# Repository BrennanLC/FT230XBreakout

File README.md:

FT230XBreakout
==============

FT230X USB to Serial Breakout Board

Please refer to FT230X datasheet for information on output pin functions
of the FT230X. Board uses SSOP package of the FT230X.

Layout tested and verified on 11/16/13

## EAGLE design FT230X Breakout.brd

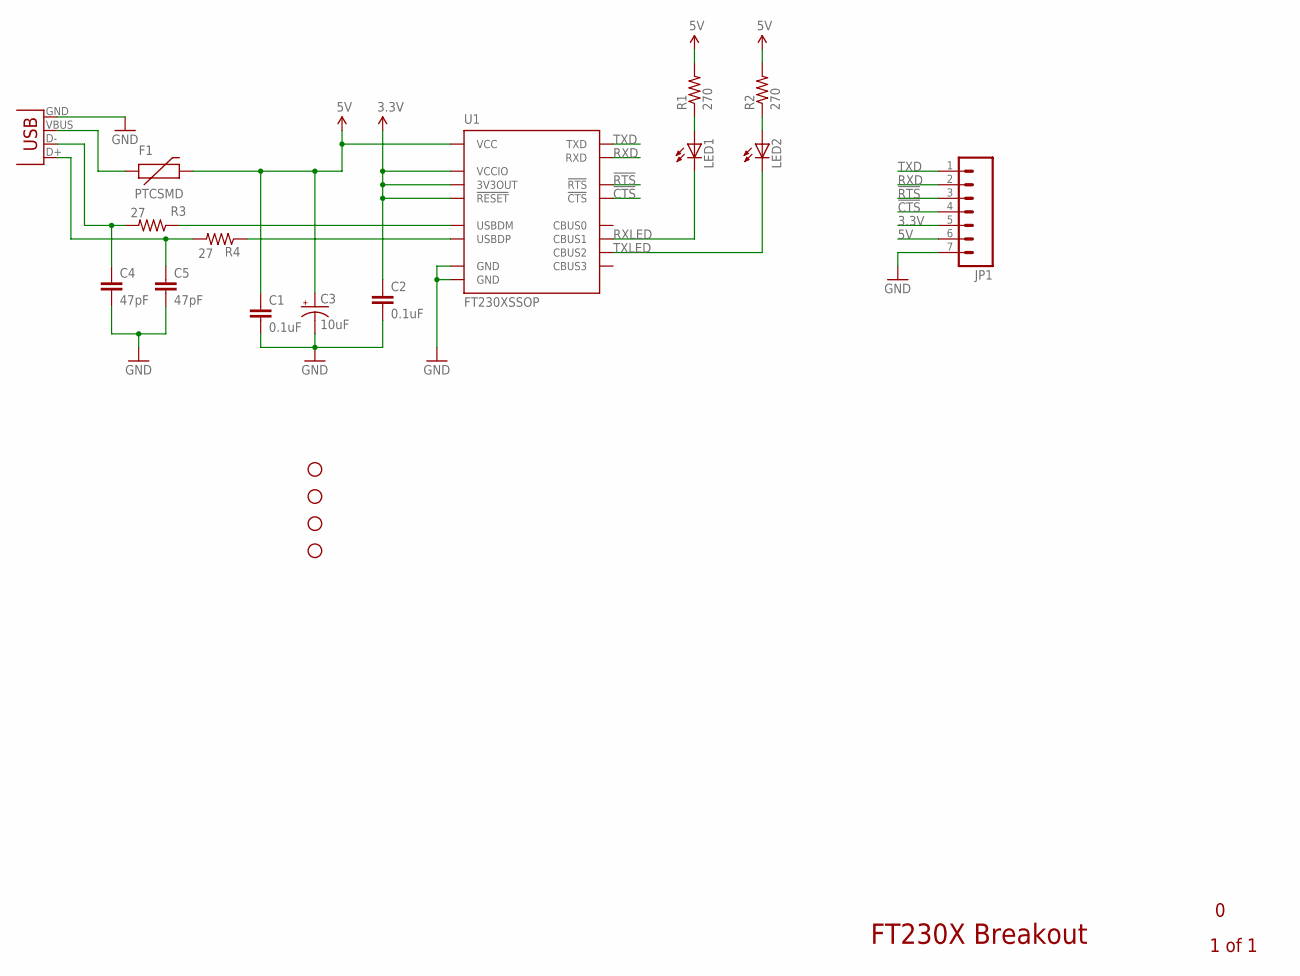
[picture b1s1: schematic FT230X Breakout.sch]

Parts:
C1, C2: 0.1uF; 0603-CAP
C3: 10uF; EIA3216-KIT
C4, C5: 47pF; 0603-CAP
F1: PTCSMD; PTC-1206
JP1: M07; 1X07
JP2: USBSMD; USB-MINIB
LED1, LED2: LED0603; LED-0603
R1, R2: 270; 0603-RES
R3, R4: 27; 0603-RES
STANDOFF1, STANDOFF2, STANDOFF3, STANDOFF4: STAND-OFF
U1: FT230XSSOP; SSOP16

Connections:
3.3V: C2.1, JP1.5, U1.3 (VCCIO), U1.10 (3V3OUT), U1.11 (!RESET)
5V: C1.1, C3.A (+), F1.2, JP1.6, R1.2, R2.2, U1.12 (VCC)
!CTS: JP1.4, U1.6 (!CTS)
!RTS: JP1.3, U1.2 (!RTS)
GND: C1.2, C2.2, C3.C (-), C4.2, C5.2, JP1.7, JP2.GND, U1.5 (GND), U1.13 (GND)
unnamed: F1.1, JP2.VBUS
unnamed: C4.1, JP2.D-, R3.2
unnamed: C5.1, JP2.D+, R4.2
unnamed: R4.1, U1.8 (USBDP)
unnamed: R3.1, U1.9 (USBDM)
unnamed: LED2.A, R2.1
unnamed: LED1.A, R1.1
RXD: JP1.2, U1.4 (RXD)
RXLED: LED1.C, U1.14 (CBUS1)
TXD: JP1.1, U1.1 (TXD)
TXLED: LED2.C, U1.7 (CBUS2)

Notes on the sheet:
FT230X Breakout
1 of 1

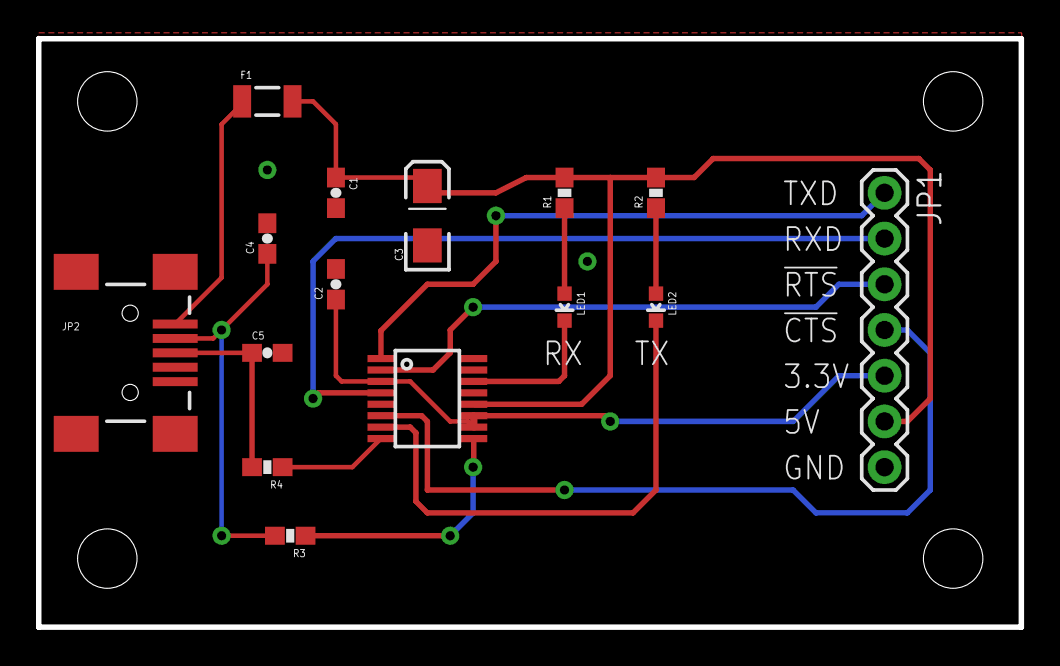
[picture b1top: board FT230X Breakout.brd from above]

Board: 2 copper layers, 54.6 x 32.7 mm, 19 parts (0 on the bottom side), 16 nets.

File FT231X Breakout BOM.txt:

Partlist exported from C:/Users/BrennanLC2/Documents/GitHub/FT231XBreakout/FT231X Breakout.sch at 11/3/2013 5:31:38 PM

Part      Value        Device           Package          Description                                                                                                                                               
C1        0.1uF        CAP0603-CAP      0603-CAP         Capacitor                                                                                                                                                 
C2        0.1uF        CAP0603-CAP      0603-CAP         Capacitor                                                                                                                                                 
C3        10uF         CAP_POL1206-KIT  EIA3216-KIT      Capacitor Polarized                                                                                                                                       
C4        47pF         CAP0603-CAP      0603-CAP         Capacitor                                                                                                                                                 
C5        47pF         CAP0603-CAP      0603-CAP         Capacitor                                                                                                                                                 
F1        PTCSMD       PTCSMD           PTC-1206         Resettable Fuse PTC                                                                                                                                       
FRAME1    FRAME-LETTER FRAME-LETTER     CREATIVE_COMMONS Schematic Frame                                                                                                                                           
JP1                    M07              1X07             Header 7                                                                                                                                                  
JP2       USBSMD       USBSMD           USB-MINIB        USB Connectors                                                                                                                                            
LED1                   LED0603          LED-0603         LEDs                                                                                                                                                      
LED2                   LED0603          LED-0603         LEDs                                                                                                                                                      
R1        270          RESISTOR0603-RES 0603-RES         Resistor                                                                                                                                                  
R2        270          RESISTOR0603-RES 0603-RES         Resistor                                                                                                                                                  
R3        27           RESISTOR0603-RES 0603-RES         Resistor                                                                                                                                                  
R4        27           RESISTOR0603-RES 0603-RES         Resistor                                                                                                                                                  
STANDOFF1 STAND-OFF    STAND-OFF        STAND-OFF        #4 Stand Off                                                                                                                                              
STANDOFF2 STAND-OFF    STAND-OFF        STAND-OFF        #4 Stand Off                                                                                                                                              
STANDOFF3 STAND-OFF    STAND-OFF        STAND-OFF        #4 Stand Off                                                                                                                                              
STANDOFF4 STAND-OFF    STAND-OFF        STAND-OFF        #4 Stand Off                                                                                                                                              
U1        FT230XSSOP   FT230XSSOP       SSOP16           The FT230X is a simple USB to serial converter IC. The CBUS lines can be used as TX and RX activity LEDs, RS485 Tx data enable, and device sleep control.

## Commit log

2013-11-04 Added Schematic and Board Files
    Added schematic and board files to the Github repository along with the
    gerber files
2013-11-04 Added BOM
    Added Bill of Materials
2013-11-04 Added extension to BOM File
2013-11-14 Updated Files
    Updated file names. Added PDF version of schematic. Changed frame in
    file.
2014-02-20 Updated BOM Files
    Updated BOM CSV and text files

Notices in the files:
parts and their libraries:
SparkFun-Connectors: Licensing: CC v3.0 Share-Alike You are welcome to use this library for commercial purposes.
